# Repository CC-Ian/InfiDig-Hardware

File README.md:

# InfiDig Hardware
An infinitely chainable 2.5 digit display made using LED Filaments and 74HC595 shift registers.

## Pinout

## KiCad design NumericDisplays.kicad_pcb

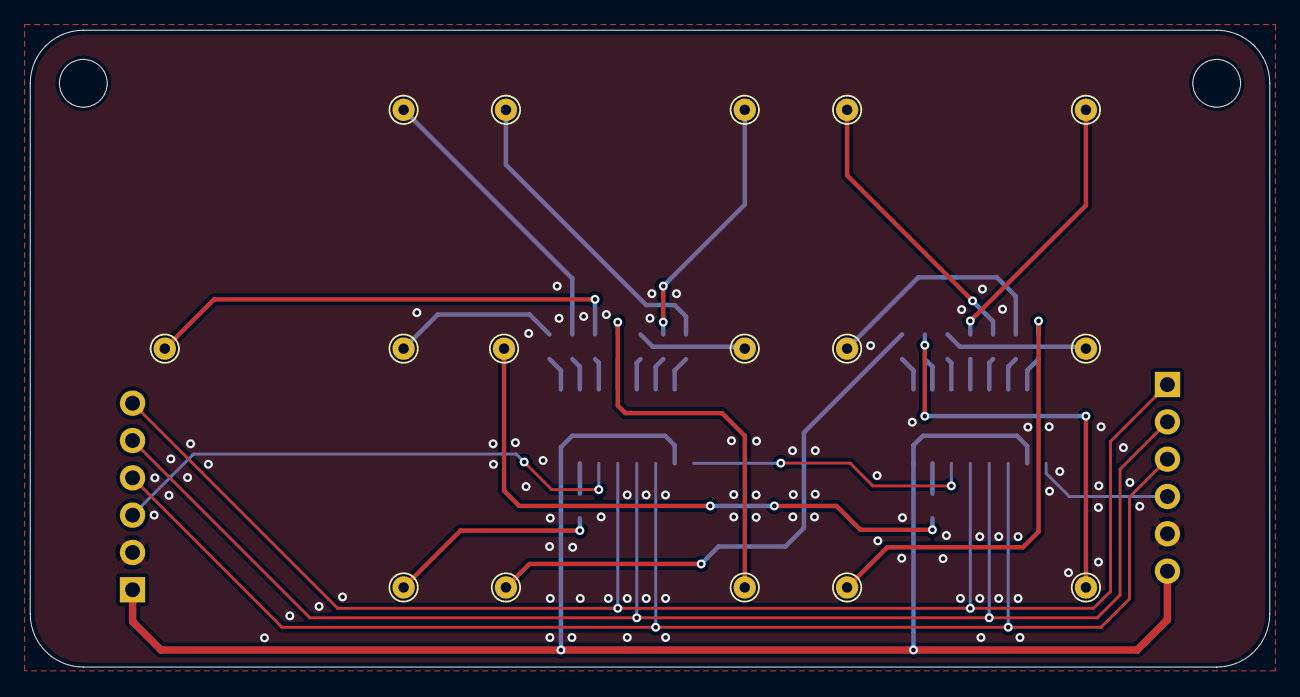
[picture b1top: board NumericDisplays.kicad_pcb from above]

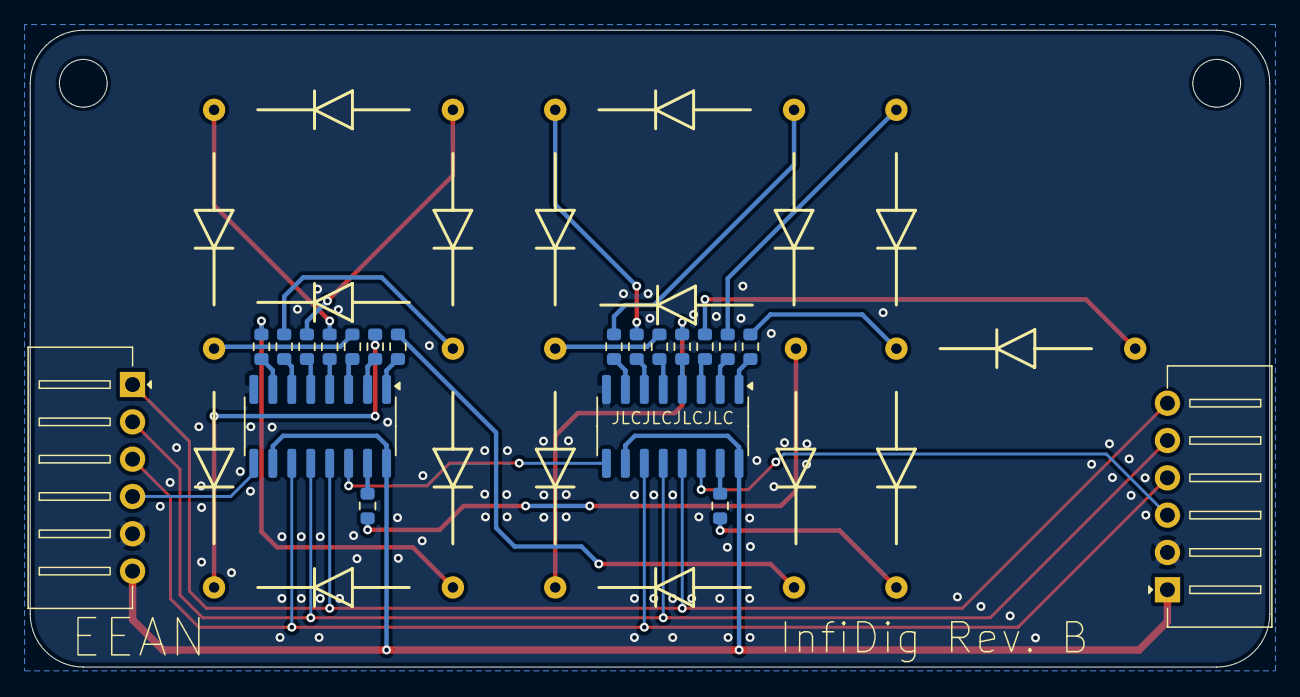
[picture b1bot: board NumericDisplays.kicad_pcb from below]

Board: 2 copper layers, 83.1 x 42.7 mm, 36 parts (20 on the bottom side), 40 nets.

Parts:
J1, J2: Conn_01x06_Pin; XH-W-06A
R1, R2, R3, R4, R5, R6, R7, R8, R9, R10, R11, R12, R13, R14, R15, R16: 22; R_0603_1608Metric
TP1, TP2, TP3, TP4, TP5, TP6, TP7, TP8, TP9, TP10, TP11, TP12, TP13, TP14, TP15, TP16: TestPoint; TestPoint_THTPad_D1.5mm_Drill0.7mm
U1, U2: 74HC595; SOIC-16_3.9x9.9mm_P1.27mm

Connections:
A0: R1.2, TP1.1
A1: R4.2, TP5.1
A2: R11.2, TP12.1
B0: R2.2, TP2.1
B1: R5.2, TP6.1
B2: R12.2, TP8.1
C0: R3.2, TP3.1
C1: R6.2, TP7.1
C2: R13.2, TP13.1
CLK: J1.4, J2.3, U1.11 (SRCLK), U2.11 (SRCLK)
D1: R7.2, TP9.1
D2: R14.2, TP14.1
Data In: J1.3, U1.14 (SER)
Data Out: J2.4, U2.9 (QH')
E0: R8.2, TP4.1
E1: R9.2, TP10.1
E2: R15.2, TP15.1
F1: R10.2, TP11.1
F2: R16.2, TP16.1
GND: J1.2, J2.5, U1.8 (GND), U2.8 (GND)
Latch: J1.5, J2.2, U1.12 (RCLK), U2.12 (RCLK)
unnamed: R1.1, U1.15 (QA)
unnamed: R2.1, U1.1 (QB)
unnamed: R3.1, U1.2 (QC)
unnamed: R8.1, U1.3 (QD)
unnamed: R4.1, U1.4 (QE)
unnamed: R5.1, U1.5 (QF)
unnamed: R6.1, U1.6 (QG)
unnamed: U1.9 (QH'), U2.14 (SER)
unnamed: R7.1, U1.7 (QH)
unnamed: R9.1, U2.15 (QA)
unnamed: R10.1, U2.1 (QB)
unnamed: R11.1, U2.2 (QC)
unnamed: R12.1, U2.3 (QD)
unnamed: R13.1, U2.4 (QE)
unnamed: R14.1, U2.5 (QF)
unnamed: R15.1, U2.6 (QG)
unnamed: R16.1, U2.7 (QH)
Output Enable: J1.6, J2.1, U1.13 (~OE), U2.13 (~OE)
VCC: J1.1, J2.6, U1.10 (~SRCLR), U1.16 (VCC), U2.10 (~SRCLR), U2.16 (VCC)

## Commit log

2024-06-20 Hardware Design Files
2024-06-23 Add product images
2024-06-23 Add pinout and readme
2024-07-15 Update to 47r resistors
2024-07-15 Add step files used for some testing.
